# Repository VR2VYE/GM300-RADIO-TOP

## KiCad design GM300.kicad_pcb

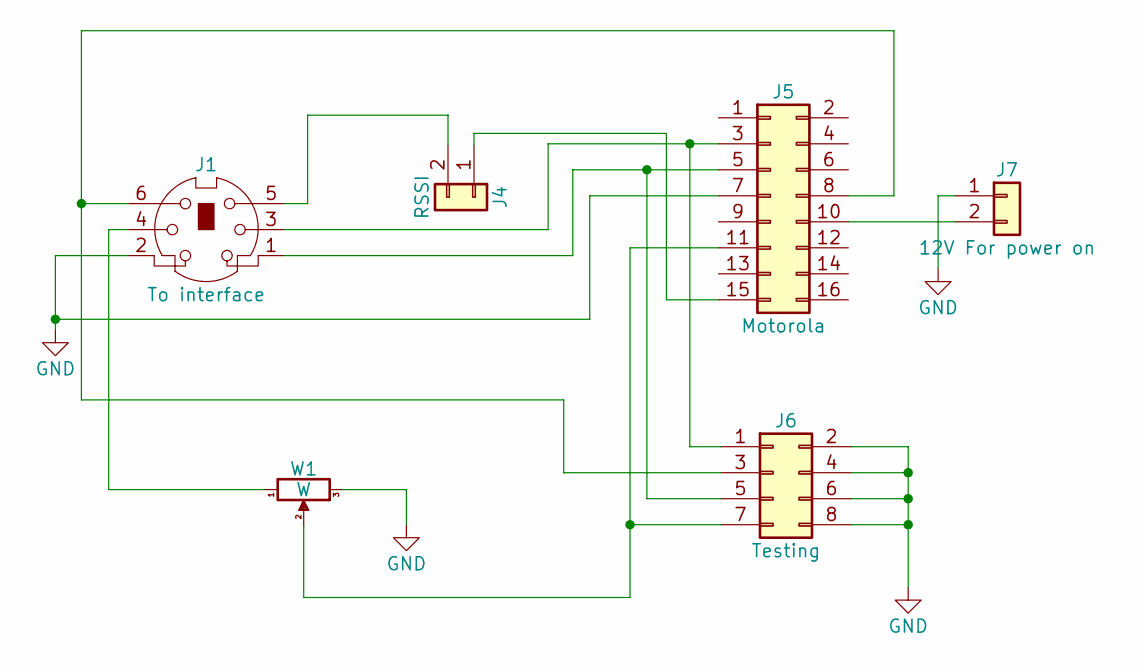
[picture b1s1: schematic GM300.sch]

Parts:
J1: To interface; ps2
J4: RSSI; Pin_Header_Straight_1x02_Pitch2.54mm
J5: Motorola; Pin_Header_Straight_2x08_Pitch2.54mm_SMD
J6: Testing; Pin_Header_Straight_2x04_Pitch2.54mm
J7: 12V For power on; Pin_Header_Straight_1x02_Pitch2.54mm
W1: W; Potentiometer_Trimmer_Vishay_T73YP_Horizontal

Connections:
GND: J1.2, J5.7, J6.2, J6.4, J6.6, J6.8, J7.1, W1.3
unnamed: J1.1, J5.5, J6.5
unnamed: J1.3, J5.3, J6.1
unnamed: J1.4, W1.1
unnamed: J1.5, J4.2
unnamed: J1.6, J5.8, J6.3
unnamed: J4.1, J5.15
unnamed: J5.10, J7.2
unnamed: J5.11, J6.7, W1.2

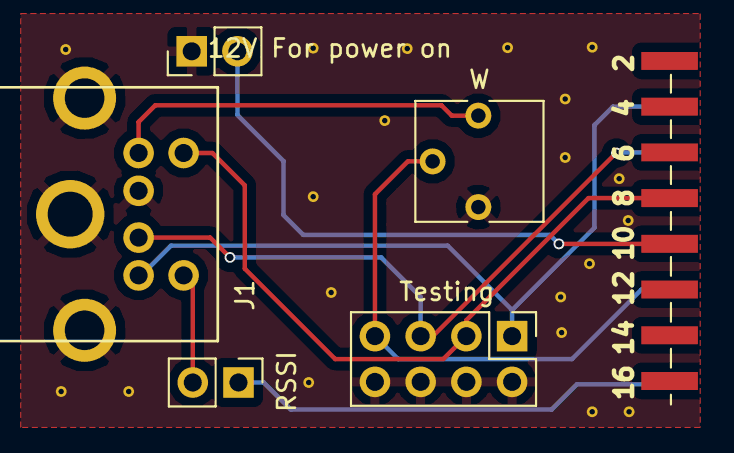
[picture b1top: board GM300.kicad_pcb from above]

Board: 2 copper layers, 6 parts (1 on the bottom side), 9 nets.
